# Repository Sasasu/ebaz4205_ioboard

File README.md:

# EBAZ4205 IO Board

IO Board for EBAZ4205

- 1 * HDMI IO
- 36 * 2.45mm GPIO
- boot selector
- build in USB2.0 to TTL
- 5v and 3.3v power supply

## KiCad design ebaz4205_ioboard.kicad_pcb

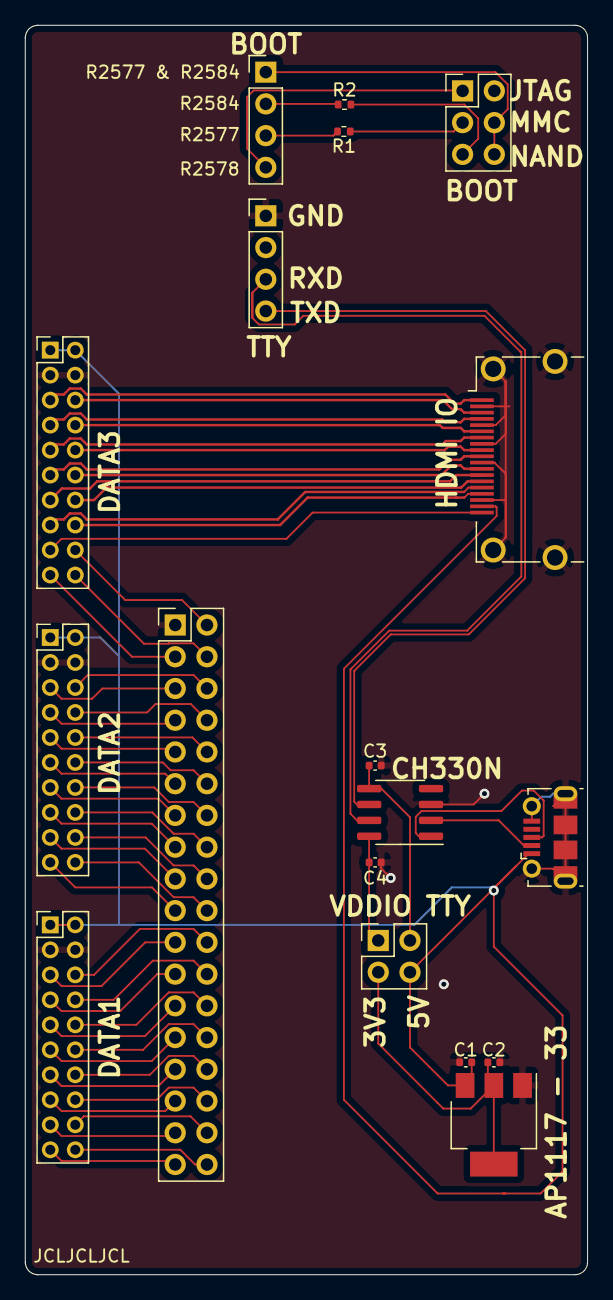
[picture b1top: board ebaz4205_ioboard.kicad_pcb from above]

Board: 2 copper layers, 45.0 x 100.0 mm, 18 parts (0 on the bottom side), 63 nets.

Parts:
C1: 10uF; C_0402_1005Metric
C2: 22uF; C_0402_1005Metric
C3, C4: 0.1uf; C_0402_1005Metric
J1: HDMI_A; HDMI_A_Amphenol_10029449-111
J2: DATA3; PinHeader_2x10_P2.00mm_Vertical
J3: DATA2; PinHeader_2x10_P2.00mm_Vertical
J4: IO; PinHeader_2x18_P2.54mm_Vertical
J5: DATA1; PinHeader_2x10_P2.00mm_Vertical
J6: BOOT_JUMP; PinHeader_1x04_P2.54mm_Vertical
J7: BOOT; PinHeader_2x03_P2.54mm_Vertical
J8: TTY; PinHeader_1x04_P2.54mm_Vertical
J9: Conn_02x02_Top_Bottom; PinHeader_2x02_P2.54mm_Vertical
J10: USB_B_Micro; USB_Micro-B_Molex-105017-0001
R1, R2: R; R_0402_1005Metric
U1: AP1117-33; SOT-223-3_TabPin2
U2: CH330N; SOIC-8_3.9x4.9mm_P1.27mm

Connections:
+3V3: C2.2, J9.3, U1.2
+5V: C1.1, J1.18, J2.1, J2.2, J3.1, J3.2, J5.1, J5.2, J9.4, J10.1, U1.3
CK+: J1.10, J2.11
CK-: J1.12, J2.12
D0+: J1.7, J2.9
D0-: J1.9, J2.10
D1+: J1.4, J2.7
D1-: J1.6, J2.8
D2+: J1.1, J2.5
D2-: J1.3, J2.6
GND: C1.2, C2.1, C3.2, C4.2, J1.2, J1.5, J1.8, J1.11, J1.17, J1.SH, J2.3, J2.4, J3.3, J3.4, J4.1, J5.3, J5.4, J7.2, J8.1, J10.5, J10.6, U1.1, U2.3
I2C+: J1.16, J2.16
I2C-: J1.15, J2.15
unnamed: C3.1, J9.2, U2.5
unnamed: C4.1, J9.1, U2.8
unnamed: J1.13, J2.13
unnamed: J1.14, J2.14
unnamed: J1.19, J2.17
unnamed: J2.18, J4.2
unnamed: J2.19, J4.3
unnamed: J2.20, J4.4
unnamed: J3.5, J4.5
unnamed: J3.6, J4.6
unnamed: J3.7, J4.7
unnamed: J3.8, J4.8
unnamed: J3.9, J4.9
unnamed: J3.10, J4.10
unnamed: J3.11, J4.11
unnamed: J3.12, J4.12
unnamed: J3.13, J4.13
unnamed: J3.14, J4.14
unnamed: J3.15, J4.15
unnamed: J3.16, J4.16
unnamed: J3.17, J4.17
unnamed: J3.18, J4.18
unnamed: J3.19, J4.19
unnamed: J3.20, J4.20
unnamed: J4.21, J5.5
unnamed: J4.22, J5.6
unnamed: J4.23, J5.7
unnamed: J4.24, J5.8
unnamed: J4.25, J5.9
unnamed: J4.26, J5.10
unnamed: J4.27, J5.11
unnamed: J4.28, J5.12
unnamed: J4.29, J5.13
unnamed: J4.30, J5.14
unnamed: J4.31, J5.15
unnamed: J4.32, J5.16
unnamed: J4.33, J5.17
unnamed: J4.34, J5.18
unnamed: J4.35, J5.19
unnamed: J4.36, J5.20
unnamed: J6.1, J7.4, J7.6
unnamed: J6.2, R2.1
unnamed: J6.3, R1.2
unnamed: J6.4, J7.1
unnamed: J7.3, R1.1
unnamed: J7.5, R2.2
RXD: J8.3, U2.7
TXD: J8.4, U2.6
USB_D+: J10.3, U2.1
USB_D-: J10.2, U2.2

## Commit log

2021-12-19 the first commit
2021-12-23 add pic
